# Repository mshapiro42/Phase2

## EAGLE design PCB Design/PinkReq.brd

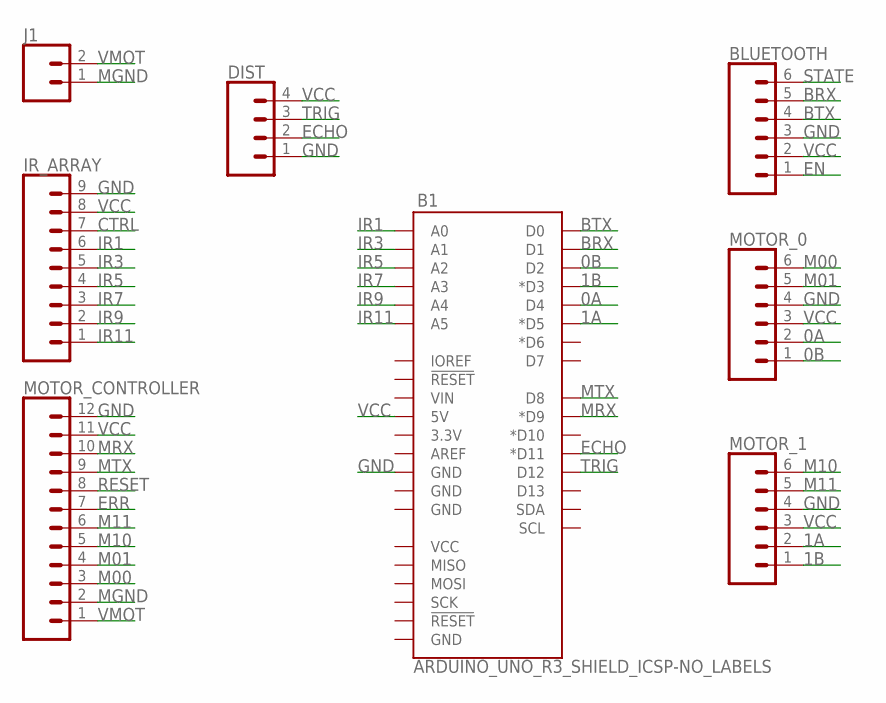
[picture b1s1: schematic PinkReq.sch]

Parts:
B1: ARDUINO_UNO_R3_SHIELD_ICSP-NO_LABELS; UNO_R3_SHIELD_ICSP_NOLABELS
BLUETOOTH: CONN_06FEMALE_LOCK; 1X06_FEMALE_LOCK.010
DIST: CONN_04LOCK; 1X04_LOCK
IR_ARRAY: CONN_09LOCK; 1X09_LOCK
J1: CONN_025MM; SCREWTERMINAL-5MM-2
MOTOR_0, MOTOR_1: CONN_06FEMALE_LOCK; 1X06_FEMALE_LOCK.010
MOTOR_CONTROLLER: CONN_12LOCK; 1X12_LOCK

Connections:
0A: B1.D4, MOTOR_0.2
0B: B1.D2, MOTOR_0.1
1A: B1.D5 (*D5), MOTOR_1.2
1B: B1.D3 (*D3), MOTOR_1.1
BRX: B1.TX (D1), BLUETOOTH.5
BTX: B1.RX (D0), BLUETOOTH.4
CTRL: IR_ARRAY.7
ECHO: B1.D11 (*D11), DIST.2
EN: BLUETOOTH.1
ERR: MOTOR_CONTROLLER.7
GND: B1.GND@2 (GND), BLUETOOTH.3, DIST.1, IR_ARRAY.9, MOTOR_0.4, MOTOR_1.4, MOTOR_CONTROLLER.12
IR1: B1.A0, IR_ARRAY.6
IR3: B1.A1, IR_ARRAY.5
IR5: B1.A2, IR_ARRAY.4
IR7: B1.A3, IR_ARRAY.3
IR9: B1.A4, IR_ARRAY.2
IR11: B1.A5, IR_ARRAY.1
M00: MOTOR_0.6, MOTOR_CONTROLLER.3
M01: MOTOR_0.5, MOTOR_CONTROLLER.4
M10: MOTOR_1.6, MOTOR_CONTROLLER.5
M11: MOTOR_1.5, MOTOR_CONTROLLER.6
MGND: J1.1, MOTOR_CONTROLLER.2
MRX: B1.D9 (*D9), MOTOR_CONTROLLER.10
MTX: B1.D8, MOTOR_CONTROLLER.9
RESET: MOTOR_CONTROLLER.8
STATE: BLUETOOTH.6
TRIG: B1.D12, DIST.3
VCC: B1.5V, BLUETOOTH.2, DIST.4, IR_ARRAY.8, MOTOR_0.3, MOTOR_1.3, MOTOR_CONTROLLER.11
VMOT: J1.2, MOTOR_CONTROLLER.1

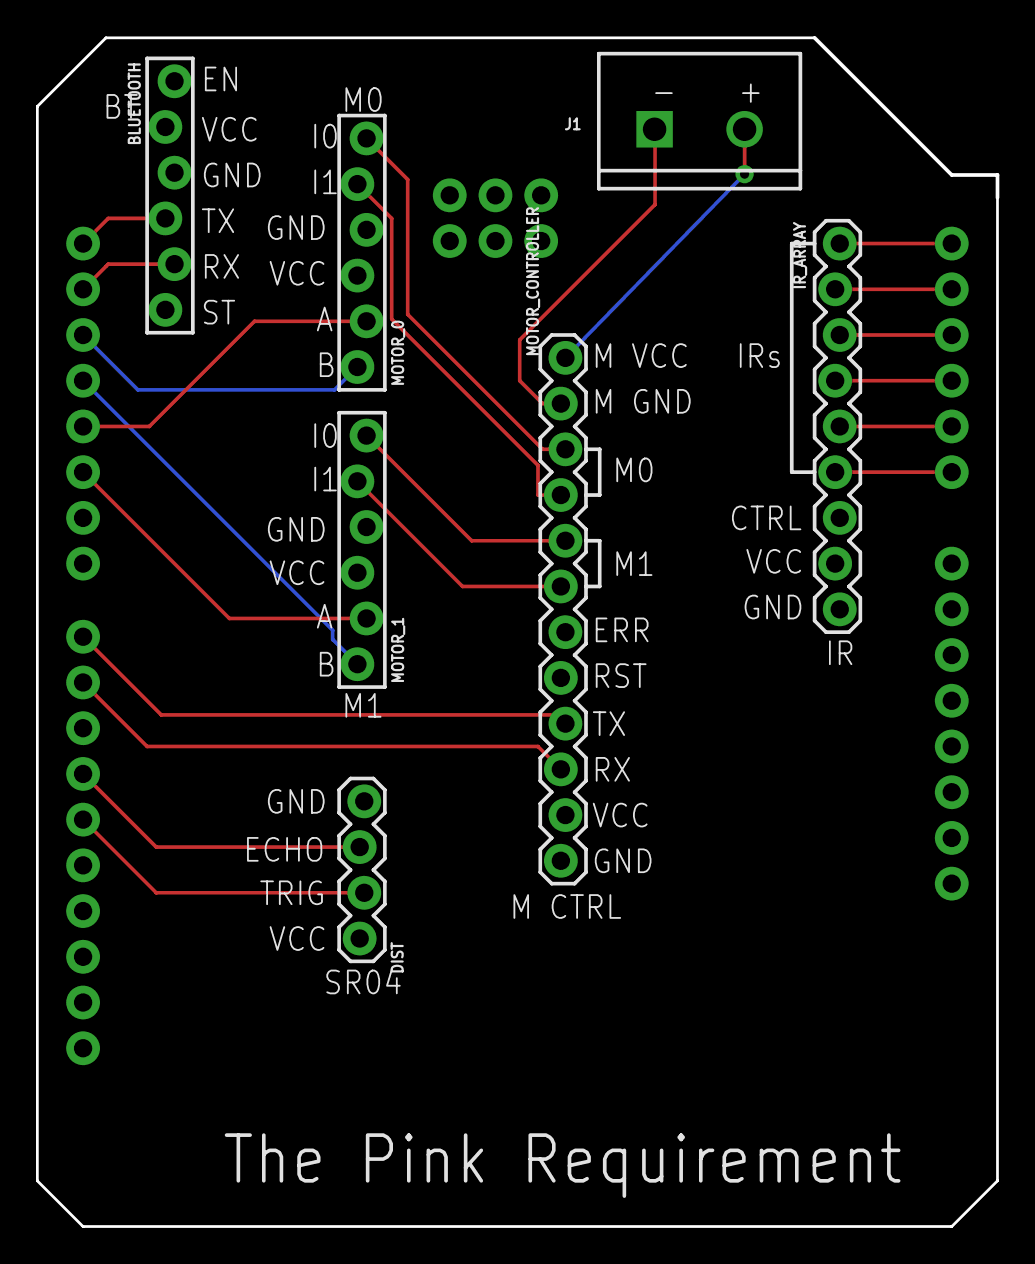
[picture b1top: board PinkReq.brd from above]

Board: 2 copper layers, 53.3 x 66.0 mm, 8 parts (0 on the bottom side), 24 nets.

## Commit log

2020-02-24 Fixed Bluetooth control issues
2020-02-25 Added test file for our encoded motors
2020-02-26 Added P control to motor testing
2020-02-29 IR examples I found and a proof of concept I did
2020-03-03 Added velocity p control file
2020-03-03 Simplified IR_LEDREAD code for arduino
2020-03-04 Added found stl files for components
2020-03-14 Code to use IR to follow line, also have code for Ultrasonic but it's commented out right now as I don't have enough cables to add it to my prototype
2020-03-25 PCB Added
2020-03-25 PCB updated with SR04
2020-03-28 Added bluetooth code
    IR code is currently commented out just to make sure bluetooth was working. Speed is just incremented, doesn't really know exactly what speed the wheels are actually creating right now
2020-03-28 Bluetooth App
    Will likely be spaced weird if you use this, so I'll work on that after higher priorities are working
2020-03-28 Bluetooth App Code
    You should be able to import this into MIT App Inventor, I haven't seen yet if there's a way to just share the same project in App Inventor
2020-04-15 Steer Control
    Line readings are really good (tested just printing those and they were great), control needs work though. Added some updated control code but haven't tested yet
2020-04-18 Ultrasonic sensor working - added control code
2020-04-22 PCB and Qik w/ BT added
2020-04-23 Control Updates
2020-04-26 Fixed Crash (I think)
2020-04-26 Fixed Crash
2020-04-26 New phase of M code
2020-04-27 Serial motors w/ J's app created
2020-04-27 Added newest code Serial motors, encoders, BT, app, and IR
2020-04-29 Updates to final prototype code
2020-04-29 Added code for ultrasonic sensor
2020-04-29 Added collision code to getVel while loop

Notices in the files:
parts and their libraries:
SparkFun-Boards: Licensing: Creative Commons ShareAlike 4.0 International - https://creativecommons.org/licenses/by-sa/4.0
